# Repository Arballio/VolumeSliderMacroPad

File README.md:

# VolumeSliderMacroPad

![alt text][logo]

[logo]: https://github.com/Arballio/VolumeSliderMacroPad/blob/main/schematic.png "Current schem visual"

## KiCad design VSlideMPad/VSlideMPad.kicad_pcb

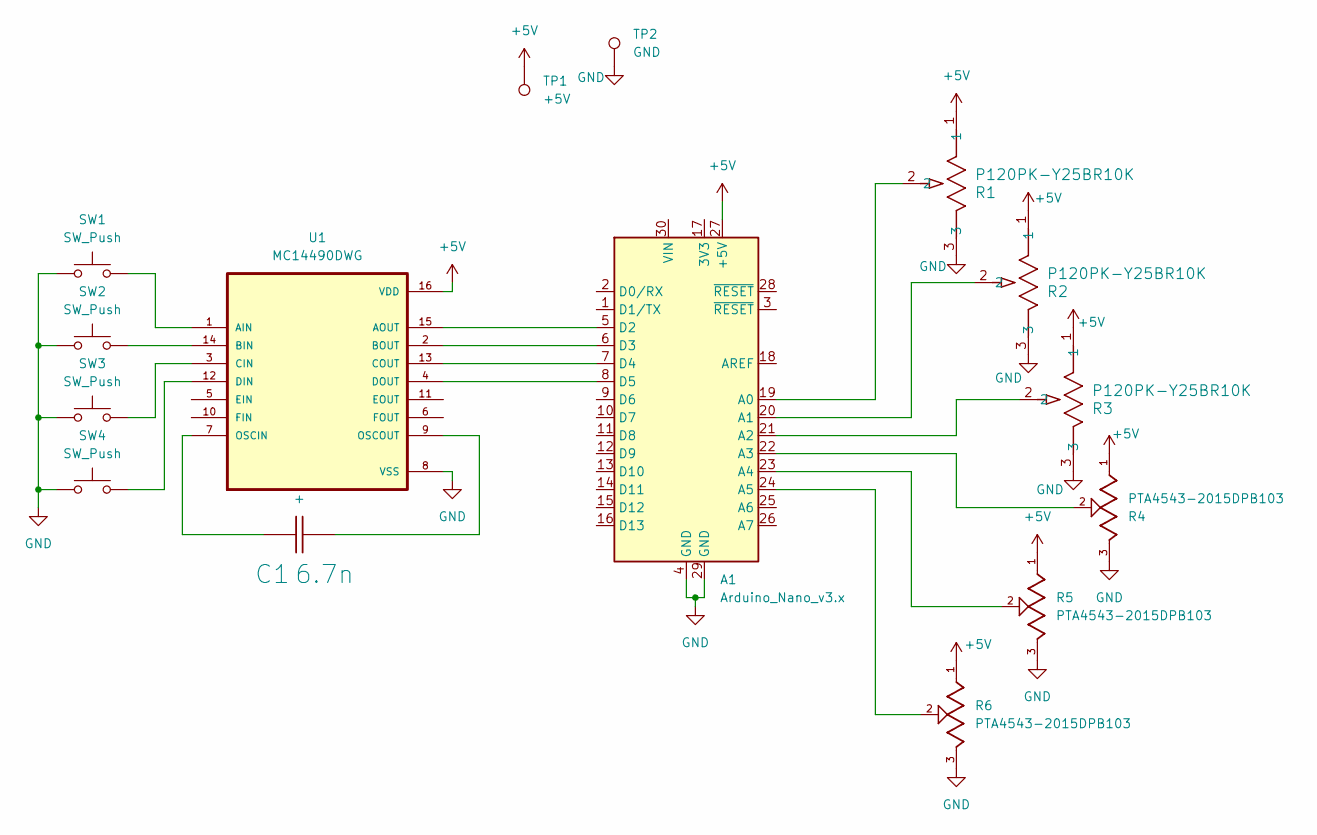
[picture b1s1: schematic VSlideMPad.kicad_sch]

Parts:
A1: Arduino_Nano_v3.x; Arduino_Nano
C1: 6.7n; C_1206
R1, R2, R3: P120PK-Y25BR10K; POT_P120PK-x25_TTE
R4, R5, R6: PTA4543-2015DPB103; TRIM_PTA4543-2015DPB103; PARTREV 04/21
SW1, SW2, SW3, SW4: SW_Push; SW_Cherry_MX_PCB_1.00u
TP1: +5V; TestPoint_Pad_06
TP2: GND; TestPoint_Pad_06
U1: MC14490DWG; SOIC127P1030X265-16N

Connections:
+5V: A1.27 (+5V), R1.1, R2.1, R3.1, R4.1, R5.1, R6.1, TP1.1, U1.16 (VDD)
GND: A1.4 (GND), A1.29 (GND), R1.3, R2.3, R3.3, R4.3, R5.3, R6.3, SW1.1, SW2.1, SW3.1, SW4.1, TP2.1, U1.8 (VSS)
unnamed: A1.19 (A0), R1.2
unnamed: A1.20 (A1), R2.2
unnamed: A1.21 (A2), R3.2
unnamed: A1.22 (A3), R4.2
unnamed: A1.23 (A4), R5.2
unnamed: A1.24 (A5), R6.2
unnamed: A1.5 (D2), U1.15 (AOUT)
unnamed: A1.6 (D3), U1.2 (BOUT)
unnamed: A1.7 (D4), U1.13 (COUT)
unnamed: A1.8 (D5), U1.4 (DOUT)
unnamed: C1.1 (+), U1.7 (OSCIN)
unnamed: C1.2 (-), U1.9 (OSCOUT)
unnamed: SW1.2, U1.1 (AIN)
unnamed: SW2.2, U1.14 (BIN)
unnamed: SW3.2, U1.3 (CIN)
unnamed: SW4.2, U1.12 (DIN)

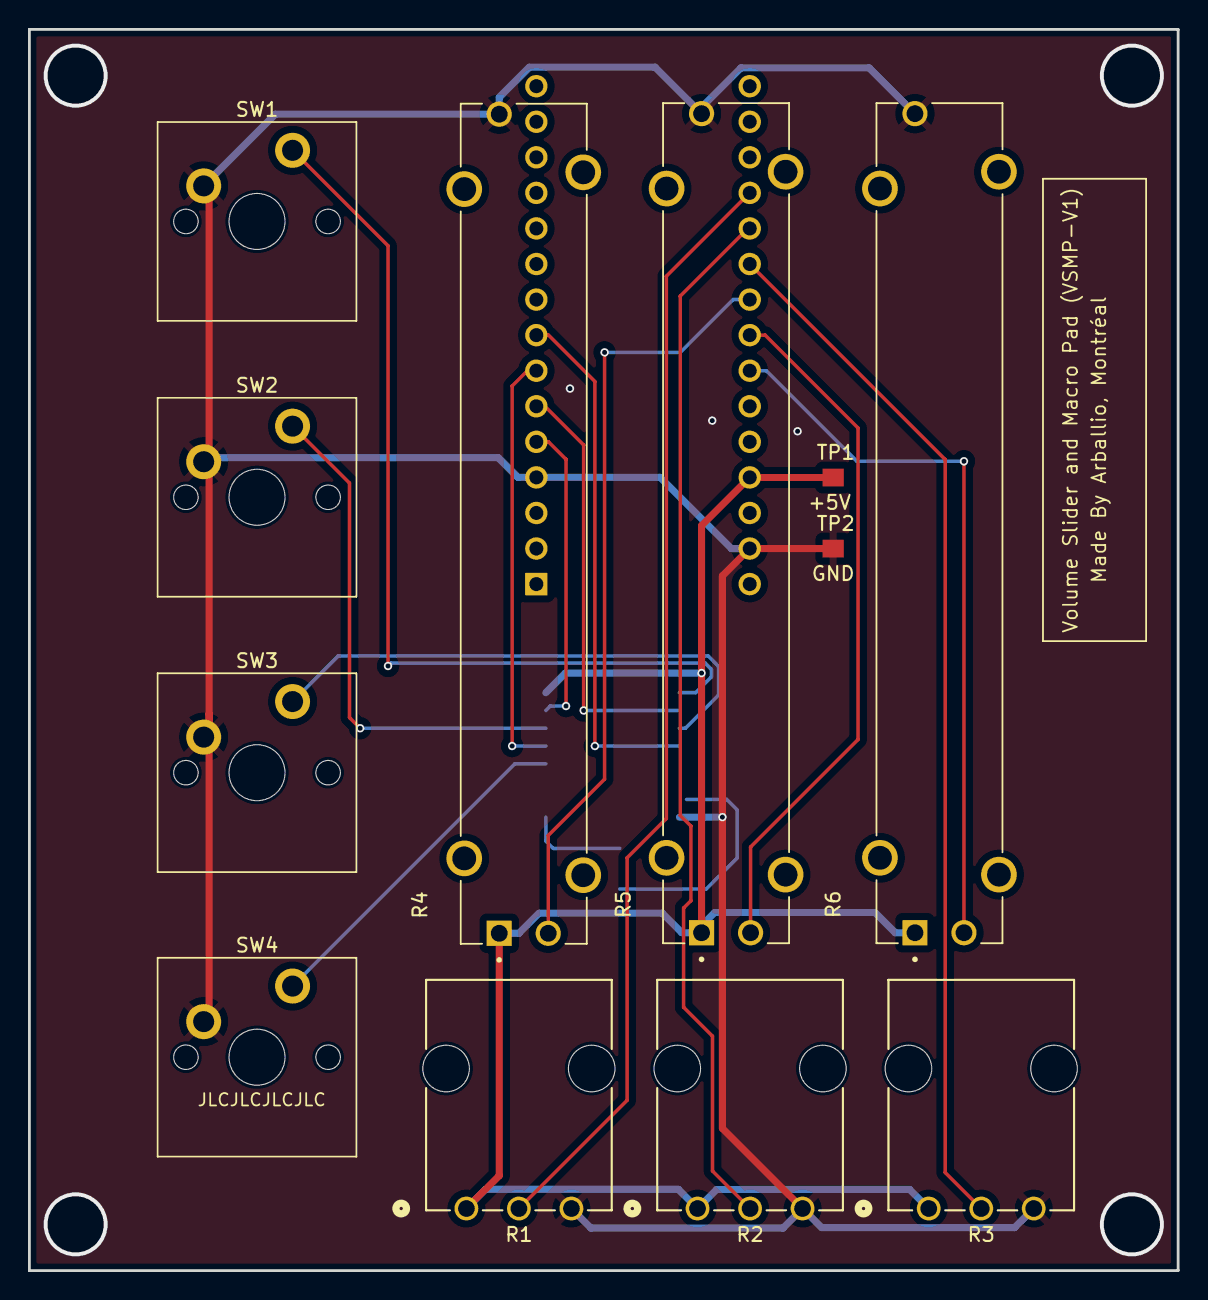
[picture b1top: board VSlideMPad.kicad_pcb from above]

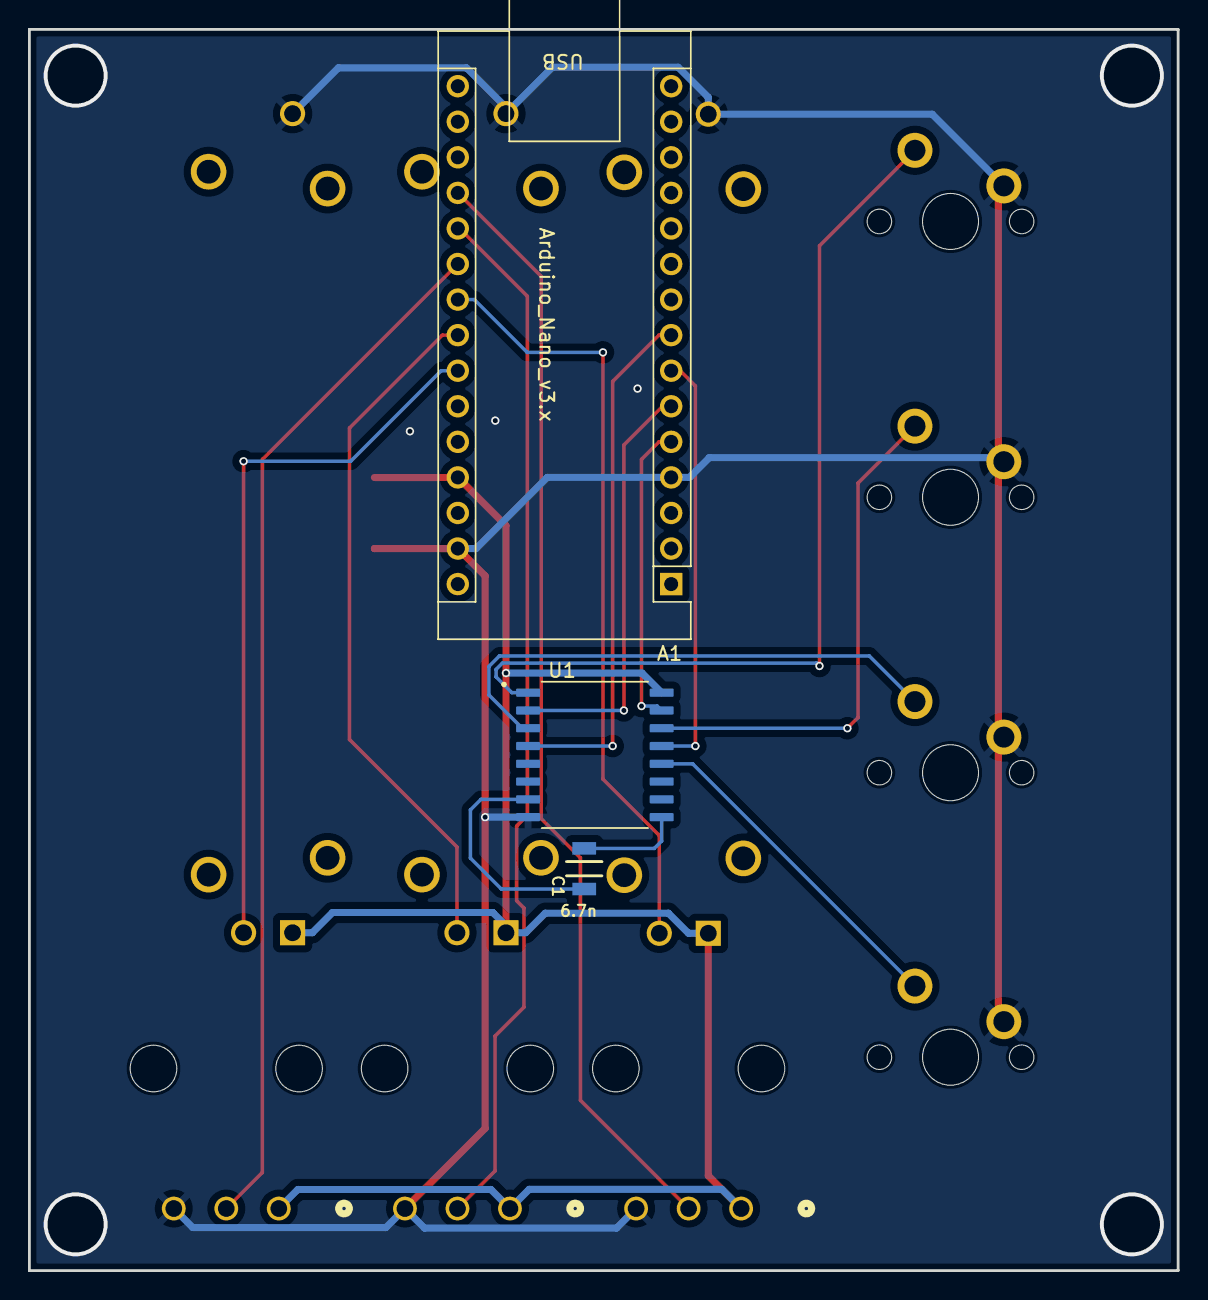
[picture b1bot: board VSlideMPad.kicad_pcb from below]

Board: 2 copper layers, 82.0 x 88.6 mm, 15 parts (3 on the bottom side), 18 nets.

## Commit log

2025-02-21 Project kicad init
2025-02-21 start of thingnymabob
2025-02-25 added pot
2025-02-28 fixed added cherry switches and fixed potentiometres
2025-03-04 board layout v1
2025-03-09 v1 routage
2025-03-12 ajout cap mc44040
2025-03-24 ignore .ick file
2025-06-28 Small layout change
2025-06-28 V1 FABRICATED
2025-07-10 Started designing a case
2025-07-10 Started designing a case
    In case folder, for solidworks
2025-07-11 Added measurements to pcb and reworked the botom case
    Note: PICK A STANDARD SIZE FOR PCB! WAY EASIER. 3230 mils by 2970 mils ?? Worse in metric
2025-07-11 Added short stud version to bottom
    Height of 1.6mm, same as PCB, makes it flush
2026-06-26 Added schem pdf into folder
2026-06-26 Update README with logo image
    Add logo image reference to README
